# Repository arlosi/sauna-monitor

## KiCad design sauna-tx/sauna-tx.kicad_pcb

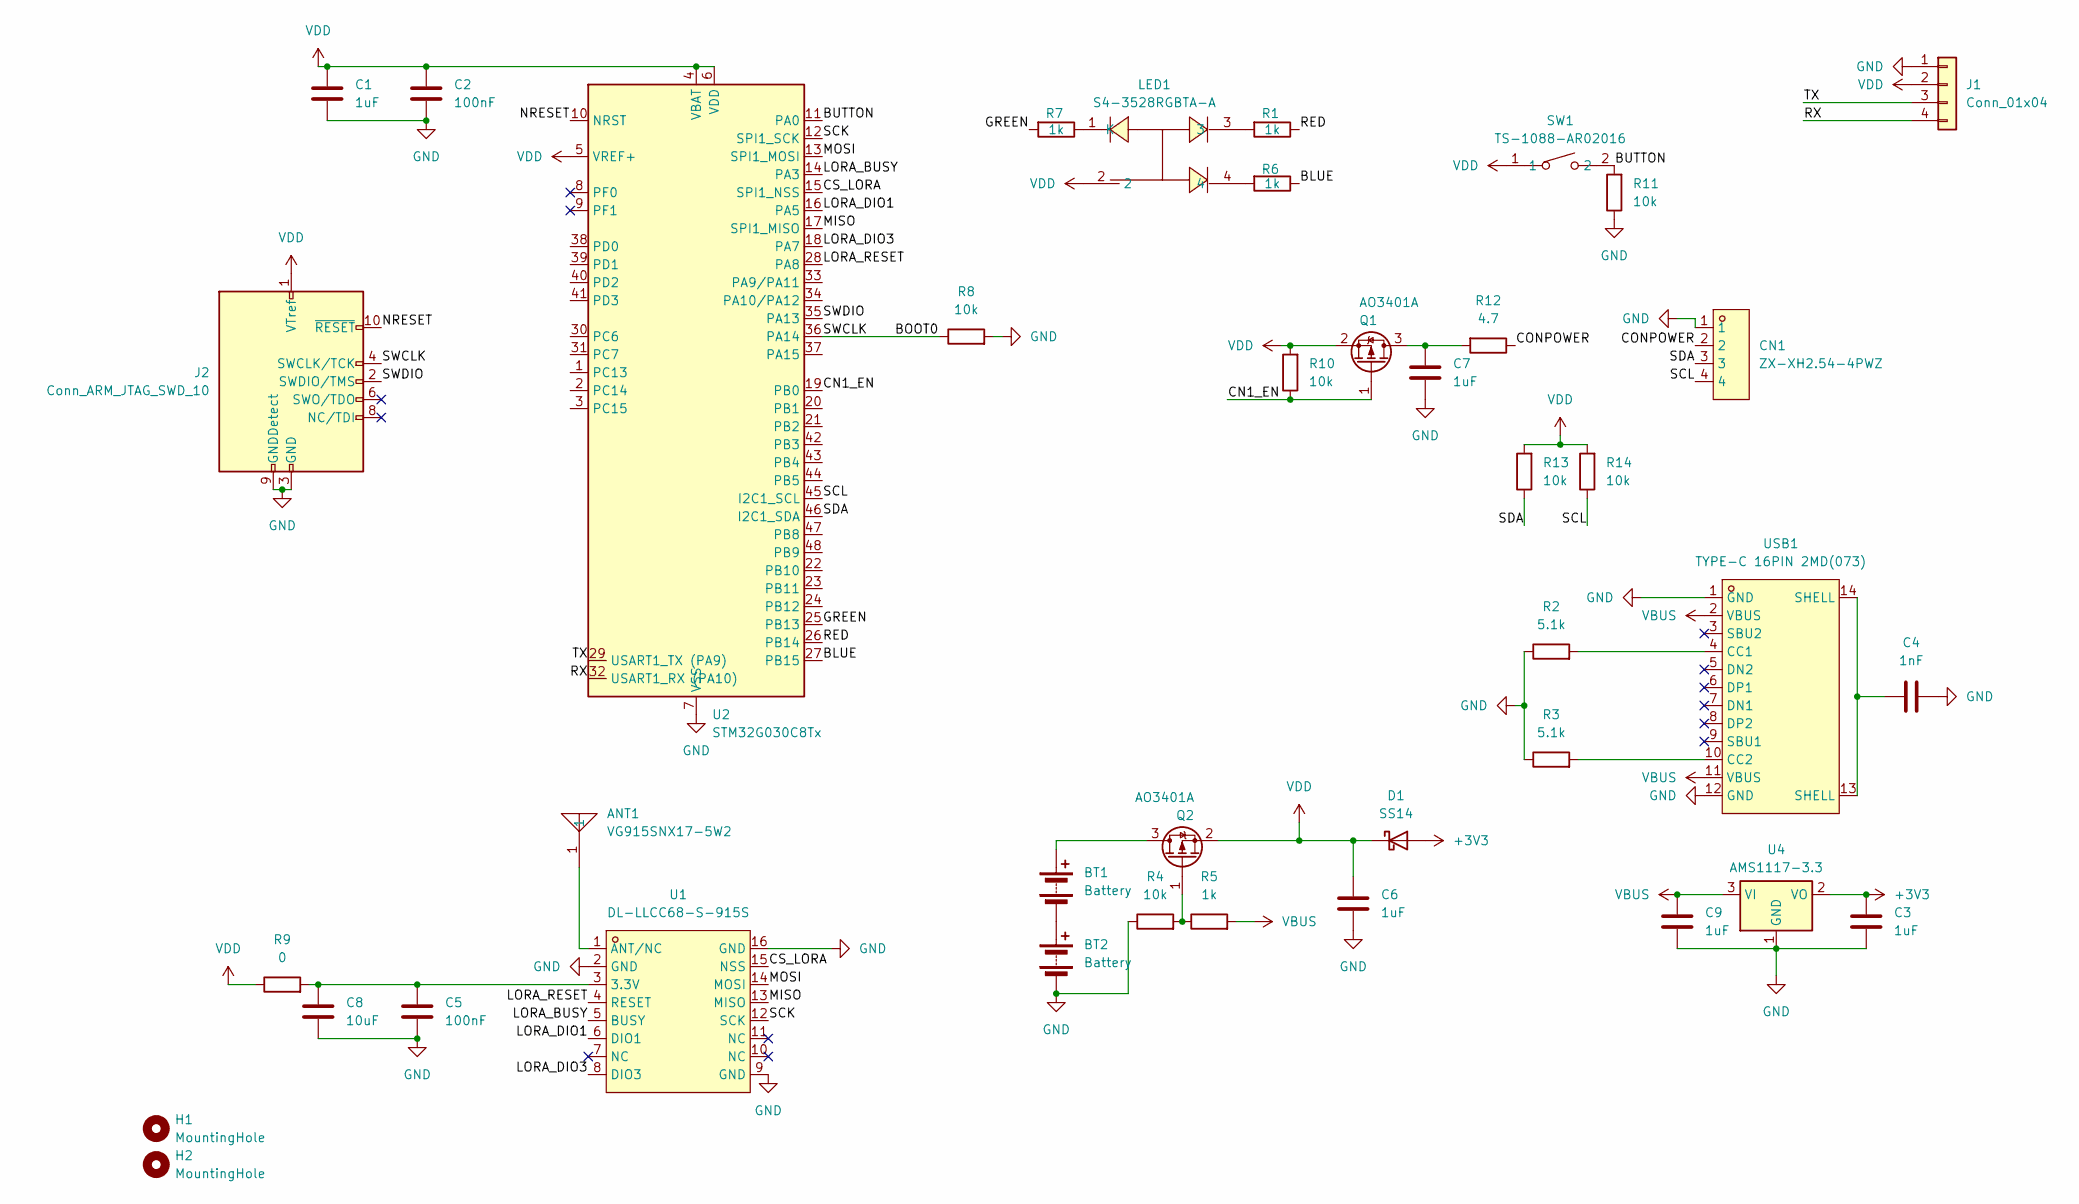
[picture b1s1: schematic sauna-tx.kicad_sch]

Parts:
ANT1: VG915SNX17-5W2; ANT-TH_BD5.5-L18.0-D0.8_470M_LORA_ANT; LCSC Part C718842
BT1, BT2: Battery; BatteryHolder_Keystone_2460_1xAA
C1, C3, C6, C7, C9: 1uF; C_0603_1608Metric
C2, C5: 100nF; C_0603_1608Metric
C4: 1nF; C_0603_1608Metric
C8: 10uF; C_0603_1608Metric
CN1: ZX-XH2.54-4PWZ; CONN-TH_4P-P2.50_ZX-XH2.54-4PWZ; LCSC Part C7429643
D1: SS14; D_SMA
H1, H2: MountingHole; MountingHole_3.2mm_M3
J1: Conn_01x04; PinHeader_1x04_P2.54mm_Vertical
J2: Conn_ARM_JTAG_SWD_10; PinHeader_2x05_P1.27mm_Vertical; LCSC Part C22373829
LED1: S4-3528RGBTA-A; LED-SMD_4P-L3.2-W2.8-LS3.5-TL-1; LCSC Part C2827321
Q1, Q2: AO3401A; SOT-23
R1, R5, R6, R7: 1k; R_0603_1608Metric
R2, R3: 5.1k; R_0603_1608Metric
R4, R8, R10, R11, R13, R14: 10k; R_0603_1608Metric
R9: 0; R_0603_1608Metric
R12: 4.7; R_0603_1608Metric
SW1: TS-1088-AR02016; SW-SMD_L3.9-W3.0-P4.45; LCSC Part C720477
U1: DL-LLCC68-S-915S; WIRELM-SMD_DL-LLCC68-S-915S; LCSC Part C22448806
U2: STM32G030C8Tx; LQFP-48_7x7mm_P0.5mm; LCSC Part C529329
U4: AMS1117-3.3; SOT-223-3_TabPin2
USB1: TYPE-C 16PIN 2MD(073); USB-C-SMD_TYPE-C-6PIN-2MD-073; LCSC Part C2765186

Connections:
+3V3: C3.1, D1.2 (A), U4.2 (VO)
/BLUE: R6.1, U2.27 (PB15)
/BOOT0: J2.4 (SWCLK/TCK), R8.1, U2.36 (PA14)
/BUTTON: R11.2, SW1.2, U2.11 (PA0)
/CN1_EN: Q1.1 (G), R10.1, U2.19 (PB0)
/CONPOWER: CN1.2, R12.1
/CS_LORA: U1.15 (NSS), U2.15 (SPI1_NSS)
/GREEN: R7.2, U2.25 (PB13)
/LORA_BUSY: U1.5 (BUSY), U2.14 (PA3)
/LORA_DIO1: U1.6 (DIO1), U2.16 (PA5)
/LORA_DIO3: U1.8 (DIO3), U2.18 (PA7)
/LORA_RESET: U1.4 (RESET), U2.28 (PA8)
/MISO: U1.13 (MISO), U2.17 (SPI1_MISO)
/MOSI: U1.14 (MOSI), U2.13 (SPI1_MOSI)
/NRESET: J2.10 (~RESET), U2.10 (NRST)
/RED: R1.1, U2.26 (PB14)
/RX: J1.4, U2.32 (USART1_RX (PA10))
/SCK: U1.12 (SCK), U2.12 (SPI1_SCK)
/SCL: CN1.4, R14.1, U2.45 (I2C1_SCL)
/SDA: CN1.3, R13.1, U2.46 (I2C1_SDA)
/SWDIO: J2.2 (SWDIO/TMS), U2.35 (PA13)
/TX: J1.3, U2.29 (USART1_TX (PA9))
GND: BT2.2 (-), C1.2, C2.2, C3.2, C4.1, C5.2, C6.2, C7.2, C8.2, C9.2, CN1.1, J1.1, J2.3 (GND), J2.5 (GND), J2.9 (GNDDetect), R2.1, R3.1, R4.1, R8.2, R11.1, U1.2 (GND), U1.9 (GND), U1.16 (GND), U2.7 (VSS), U4.1 (GND), USB1.1 (GND), USB1.12 (GND)
unnamed: BT1.1 (+), Q2.3 (D)
unnamed: BT1.2 (-), BT2.1 (+)
unnamed: C4.2, USB1.13 (SHELL), USB1.14 (SHELL)
unnamed: LED1.1 (K), R7.1
unnamed: LED1.3, R1.2
unnamed: LED1.4, R6.2
unnamed: C7.1, Q1.3 (D), R12.2
unnamed: Q2.1 (G), R4.2, R5.1
unnamed: C5.1, C8.1, R9.2, U1.3 (3.3V)
unnamed: ANT1.1, U1.1 (ANT/NC)
unnamed: R2.2, USB1.4 (CC1)
unnamed: R3.2, USB1.10 (CC2)
VBUS: C9.1, R5.2, U4.3 (VI), USB1.2 (VBUS), USB1.11 (VBUS)
VDD: C1.1, C2.1, C6.1, D1.1 (K), J1.2, J2.1 (VTref), LED1.2, Q1.2 (S), Q2.2 (S), R9.1, R10.2, R13.2, R14.2, SW1.1, U2.4 (VBAT), U2.5 (VREF+), U2.6 (VDD)

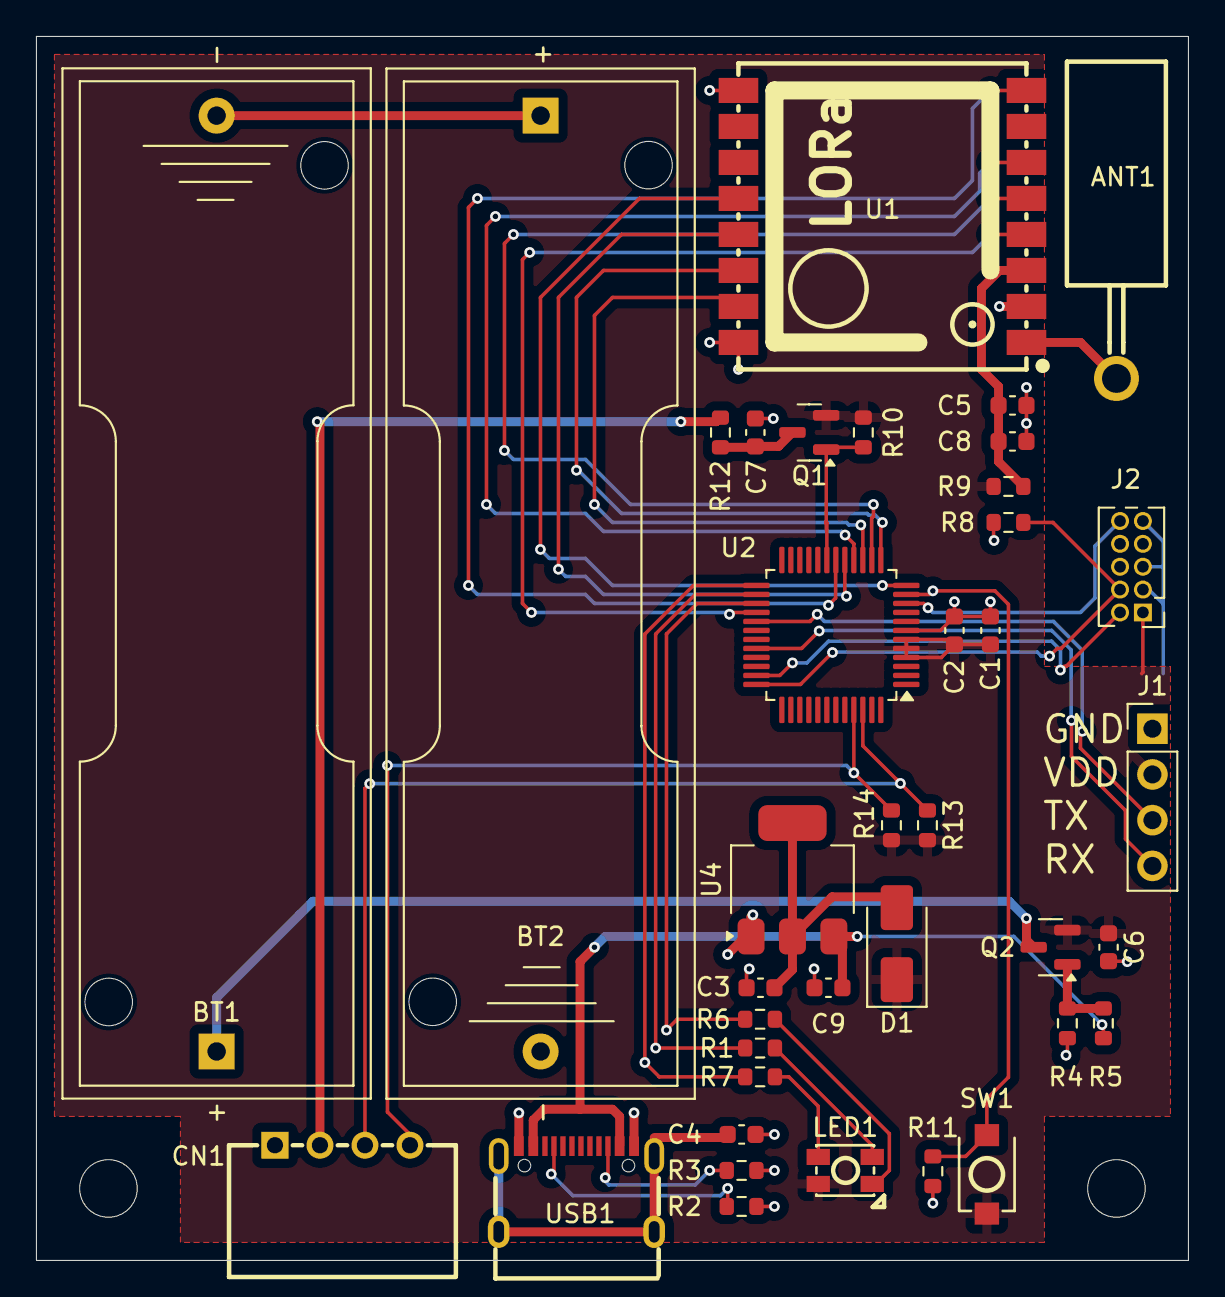
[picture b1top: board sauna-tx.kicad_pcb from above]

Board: 2 copper layers, 64.0 x 68.0 mm, 40 parts (0 on the bottom side), 37 nets.

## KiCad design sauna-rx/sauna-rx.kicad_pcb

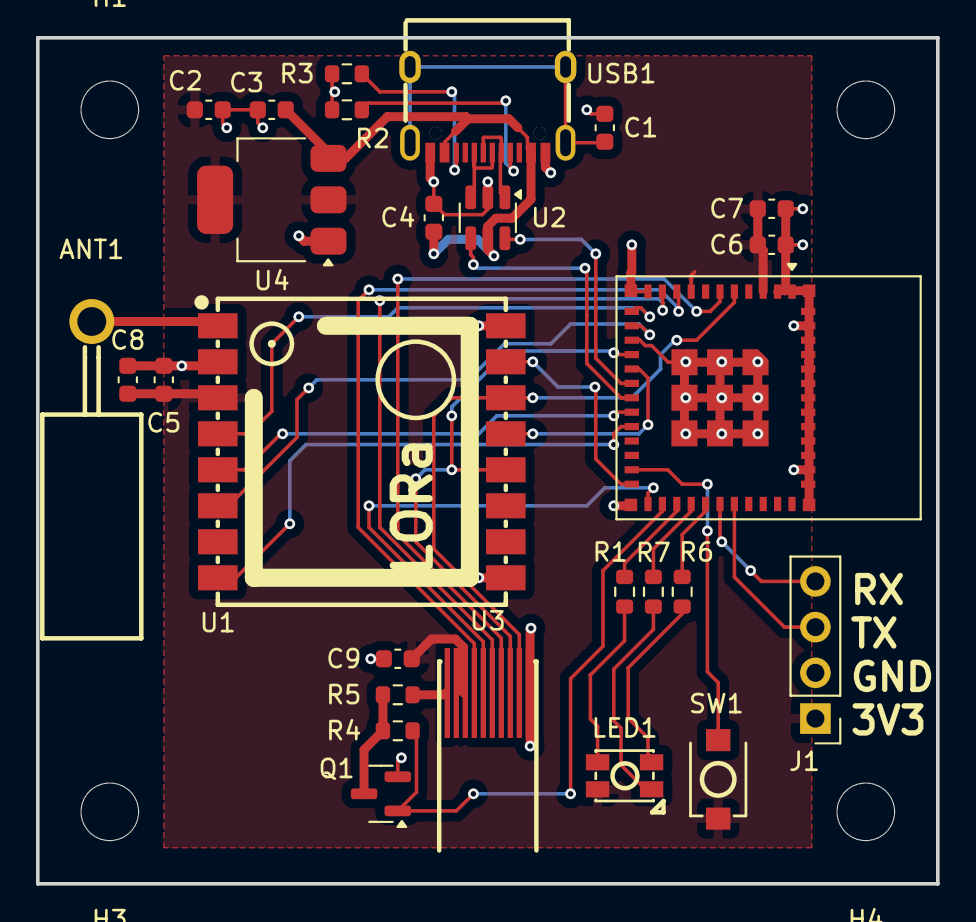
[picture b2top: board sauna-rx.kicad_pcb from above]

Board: 2 copper layers, 50.0 x 47.0 mm, 31 parts (0 on the bottom side), 35 nets.

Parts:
ANT1: VG915SNX17-5W2; ANT-TH_BD5.5-L18.0-D0.8_470M_LORA_ANT
C1: 1nF; C_0603_1608Metric
C2, C3, C9: 1uF; C_0603_1608Metric
C4, C5, C7: 100nF; C_0603_1608Metric
C6, C8: 10uF; C_0603_1608Metric
H1, H2, H3, H4: MountingHole; MountingHole_3.2mm_M3
J1: Conn_01x04; PinHeader_1x04_P2.54mm_Vertical
LED1: S4-3528RGBTA-A; LED-SMD_4P-L3.2-W2.8-LS3.5-TL-1
Q1: AO3400A; SOT-23
R1, R6, R7: 1k; R_0603_1608Metric
R2, R3: 5.1k; R_0603_1608Metric
R4: 10k; R_0603_1608Metric
R5: 4.7; R_0603_1608Metric
SW1: TS-1088-AR02016; SW-SMD_L3.9-W3.0-P4.45
U1: DL-LLCC68-S-915S; WIRELM-SMD_DL-LLCC68-S-915S
U2: USBLC6-2SC6; SOT-23-6
U3: HS17QS178RX; OLED-SMD_10P-P0.50_HS17QS178RX
U4: AMS1117-3.3; SOT-223-3_TabPin2
U6: ESP32-C6-MINI-1
USB1: TYPE-C 16PIN 2MD(073); USB-C-SMD_TYPE-C-6PIN-2MD-073

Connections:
+3V3: C2.1, C5.1, C6.1, C7.1, C8.1, C9.1, J1.1, LED1.2, SW1.1, U1.3 (3.3V), U3.2 (LEDA), U3.3 (VDD3.3V), U4.2 (VO), U6.3 (3V3), U6.8 (EN)
/BLUE: R1.2, U6.27 (IO21)
/BUTTON: SW1.2, U6.23 (IO9)
/CS_DISPLAY: U3.5 (CS), U6.25 (IO19)
/CS_LORA: U1.15 (NSS), U6.24 (IO18)
/DISPLAY_BACKLIGHT: Q1.1 (G), R4.1, U6.26 (IO20)
/DISPLAY_DC: U3.7 (D/CX), U6.6 (IO3)
/DISPLAY_RESET: U3.6 (RESET), U6.10 (IO5)
/DISPLAY_TE: U3.4 (TE), U6.9 (IO4)
/DN: U2.1 (I/O1), USB1.5 (DN2), USB1.7 (DN1)
/DP: U2.3 (I/O2), USB1.6 (DP1), USB1.8 (DP2)
/GREEN: R6.1, U6.29 (IO23)
/LORA_BUSY: U1.5 (BUSY), U6.19 (IO14)
/LORA_DIO1: U1.6 (DIO1), U6.13 (IO1)
/LORA_DIO3: U1.8 (DIO3), U6.20 (IO15)
/LORA_RESET: U1.4 (RESET), U6.12 (IO0)
/MISO: U1.13 (MISO), U6.16 (IO7)
/MOSI: U1.14 (MOSI), U3.9 (SDA), U6.5 (IO2)
/RED: R7.1, U6.28 (IO22)
/RX: J1.4, U6.30 (RXD0)
/SCK: U1.12 (SCK), U3.8 (SCLK), U6.15 (IO6)
/TX: J1.3, U6.31 (TXD0)
/USBD+: U2.4 (I/O2), U6.18 (IO13)
/USBD-: U2.6 (I/O1), U6.17 (IO12)
GND: C1.1, C2.2, C3.2, C4.2, C5.2, C6.2, C7.2, C8.2, C9.2, J1.2, Q1.2 (S), R2.1, R3.1, U1.2 (GND), U1.9 (GND), U1.16 (GND), U2.2 (GND), U3.10 (GND), U4.1 (GND), U6.1 (GND), U6.2 (GND), U6.11 (GND), U6.14 (GND), U6.36 (GND), U6.37 (GND), U6.38 (GND), U6.39 (GND), U6.40 (GND), U6.41 (GND), U6.42 (GND), U6.43 (GND), U6.44 (GND), U6.45 (GND), U6.46 (GND), U6.47 (GND), U6.48 (GND), U6.49 (GND), U6.50 (GND), U6.51 (GND), U6.52 (GND), U6.53 (GND), USB1.1 (GND), USB1.12 (GND)
unnamed: C1.2, USB1.13 (SHELL), USB1.14 (SHELL)
unnamed: LED1.1 (K), R1.1
unnamed: LED1.3, R6.2
unnamed: LED1.4, R7.2
unnamed: Q1.3 (D), R4.2, R5.1
unnamed: ANT1.1, U1.1 (ANT/NC)
unnamed: R5.2, U3.1 (LEDK)
unnamed: R2.2, USB1.4 (CC1)
unnamed: R3.2, USB1.10 (CC2)
VBUS: C3.1, C4.1, U2.5 (VBUS), U4.3 (VI), USB1.2 (VBUS), USB1.11 (VBUS)
